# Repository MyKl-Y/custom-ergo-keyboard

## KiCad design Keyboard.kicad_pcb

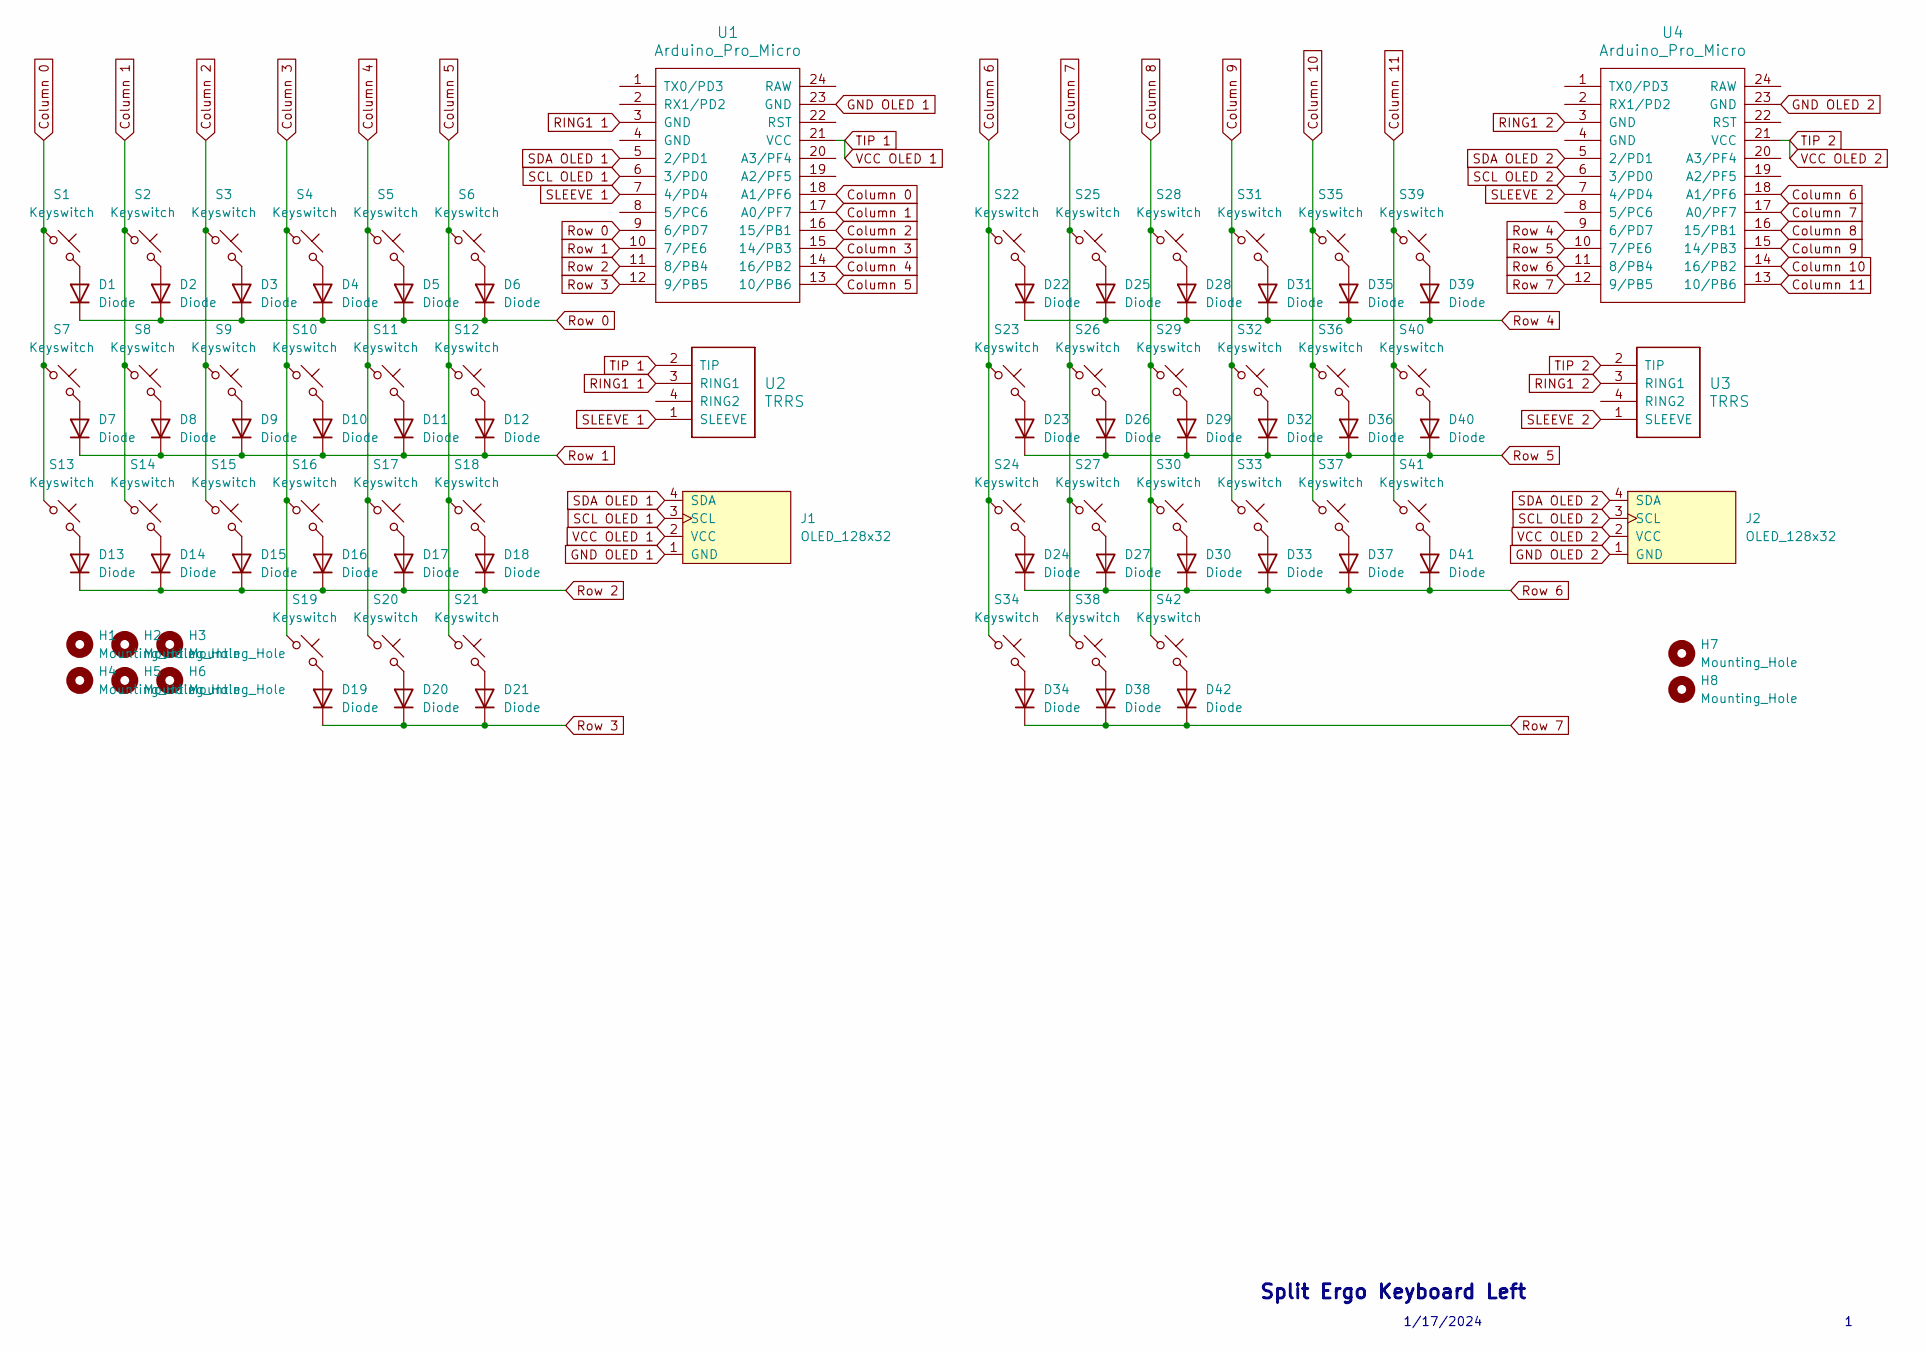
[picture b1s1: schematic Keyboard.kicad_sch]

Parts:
D1, D2, D3, D4, D5, D6, D7, D8, D9, D10, D11, D12, D13, D14, D15, D16, D17, D18, D19, D20, D21, D22, D23, D24, D25, D26, D27, D28, D29, D30, D31, D32, D33, D34, D35, D36, D37, D38, D39, D40, D41, D42: Diode; Diode_DO-35
H1, H2, H3, H4, H5, H6, H7, H8: Mounting_Hole; MountingHole_2mm
J1, J2: OLED_128x32
S1, S2, S3, S4, S5, S6, S7, S8, S9, S10, S11, S12, S13, S14, S15, S16, S17, S18, S19, S20, S22, S23, S24, S25, S26, S27, S28, S29, S30, S31, S32, S33, S35, S36, S37, S38, S39, S40, S41, S42: Keyswitch; Choc_Mini_1.00u
S21, S34: Keyswitch; Choc_Mini_1.25u
U1, U4: Arduino_Pro_Micro
U2, U3: TRRS; TRRS_PJ-320A

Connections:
Column 0: S1.1, S7.1, S13.1, U1.18 (A1/PF6)
Column 1: S2.1, S8.1, S14.1, U1.17 (A0/PF7)
Column 2: S3.1, S9.1, S15.1, U1.16 (15/PB1)
Column 3: S4.1, S10.1, S16.1, S19.1, U1.15 (14/PB3)
Column 4: S5.1, S11.1, S17.1, S20.1, U1.14 (16/PB2)
Column 5: S6.1, S12.1, S18.1, S21.1, U1.13 (10/PB6)
Column 6: S22.1, S23.1, S24.1, S34.1, U4.18 (A1/PF6)
Column 7: S25.1, S26.1, S27.1, S38.1, U4.17 (A0/PF7)
Column 8: S28.1, S29.1, S30.1, S42.1, U4.16 (15/PB1)
Column 9: S31.1, S32.1, S33.1, U4.15 (14/PB3)
Column 10: S35.1, S36.1, S37.1, U4.14 (16/PB2)
Column 11: S39.1, S40.1, S41.1, U4.13 (10/PB6)
GND OLED 1: J1.1 (GND), U1.23 (GND)
GND OLED 2: J2.1 (GND), U4.23 (GND)
unnamed: D1.2 (A), S1.2
unnamed: D2.2 (A), S2.2
unnamed: D3.2 (A), S3.2
unnamed: D4.2 (A), S4.2
unnamed: D5.2 (A), S5.2
unnamed: D6.2 (A), S6.2
unnamed: D7.2 (A), S7.2
unnamed: D8.2 (A), S8.2
unnamed: D9.2 (A), S9.2
unnamed: D10.2 (A), S10.2
unnamed: D11.2 (A), S11.2
unnamed: D12.2 (A), S12.2
unnamed: D13.2 (A), S13.2
unnamed: D14.2 (A), S14.2
unnamed: D15.2 (A), S15.2
unnamed: D16.2 (A), S16.2
unnamed: D17.2 (A), S17.2
unnamed: D18.2 (A), S18.2
unnamed: D19.2 (A), S19.2
unnamed: D20.2 (A), S20.2
unnamed: D21.2 (A), S21.2
unnamed: D22.2 (A), S22.2
unnamed: D23.2 (A), S23.2
unnamed: D24.2 (A), S24.2
unnamed: D25.2 (A), S25.2
unnamed: D26.2 (A), S26.2
unnamed: D27.2 (A), S27.2
unnamed: D28.2 (A), S28.2
unnamed: D29.2 (A), S29.2
unnamed: D30.2 (A), S30.2
unnamed: D31.2 (A), S31.2
unnamed: D32.2 (A), S32.2
unnamed: D33.2 (A), S33.2
unnamed: D34.2 (A), S34.2
unnamed: D35.2 (A), S35.2
unnamed: D36.2 (A), S36.2
unnamed: D37.2 (A), S37.2
unnamed: D38.2 (A), S38.2
unnamed: D39.2 (A), S39.2
unnamed: D40.2 (A), S40.2
unnamed: D41.2 (A), S41.2
unnamed: D42.2 (A), S42.2
RING1 1: U1.3 (GND), U2.3 (RING1)
RING1 2: U3.3 (RING1), U4.3 (GND)
Row 0: D1.1 (K), D2.1 (K), D3.1 (K), D4.1 (K), D5.1 (K), D6.1 (K), U1.9 (6/PD7)
Row 1: D7.1 (K), D8.1 (K), D9.1 (K), D10.1 (K), D11.1 (K), D12.1 (K), U1.10 (7/PE6)
Row 2: D13.1 (K), D14.1 (K), D15.1 (K), D16.1 (K), D17.1 (K), D18.1 (K), U1.11 (8/PB4)
Row 3: D19.1 (K), D20.1 (K), D21.1 (K), U1.12 (9/PB5)
Row 4: D22.1 (K), D25.1 (K), D28.1 (K), D31.1 (K), D35.1 (K), D39.1 (K), U4.9 (6/PD7)
Row 5: D23.1 (K), D26.1 (K), D29.1 (K), D32.1 (K), D36.1 (K), D40.1 (K), U4.10 (7/PE6)
Row 6: D24.1 (K), D27.1 (K), D30.1 (K), D33.1 (K), D37.1 (K), D41.1 (K), U4.11 (8/PB4)
Row 7: D34.1 (K), D38.1 (K), D42.1 (K), U4.12 (9/PB5)
SCL OLED 1: J1.3 (SCL), U1.6 (3/PD0)
SCL OLED 2: J2.3 (SCL), U4.6 (3/PD0)
SDA OLED 1: J1.4 (SDA), U1.5 (2/PD1)
SDA OLED 2: J2.4 (SDA), U4.5 (2/PD1)
SLEEVE 1: U1.7 (4/PD4), U2.1 (SLEEVE)
SLEEVE 2: U3.1 (SLEEVE), U4.7 (4/PD4)
TIP 1: J1.2 (VCC), U1.21 (VCC), U2.2 (TIP)
TIP 2: J2.2 (VCC), U3.2 (TIP), U4.21 (VCC)

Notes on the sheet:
1/17/2024
Split Ergo Keyboard Left

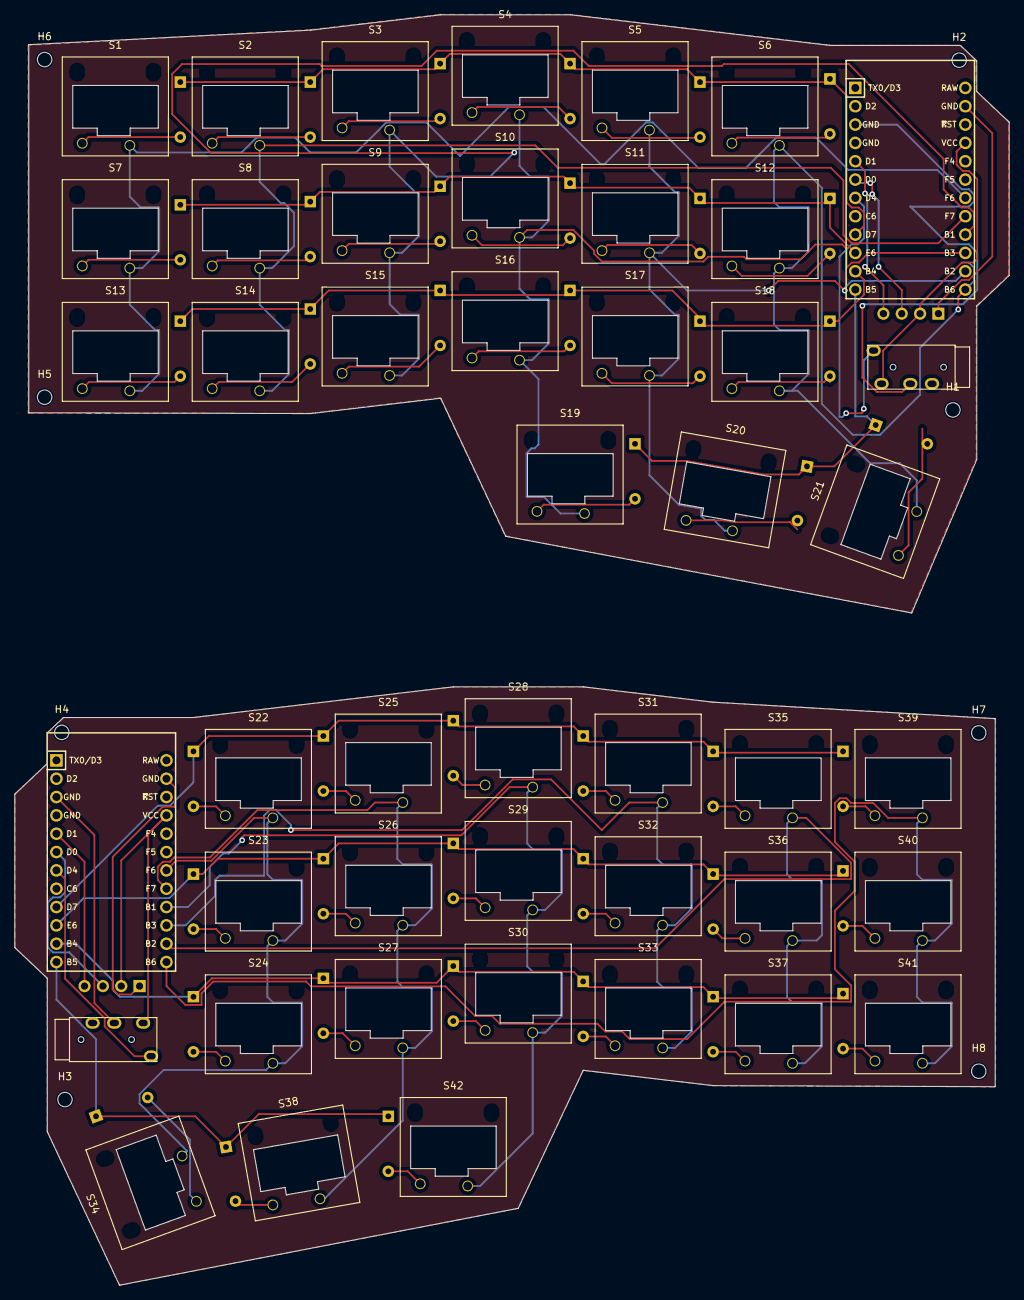
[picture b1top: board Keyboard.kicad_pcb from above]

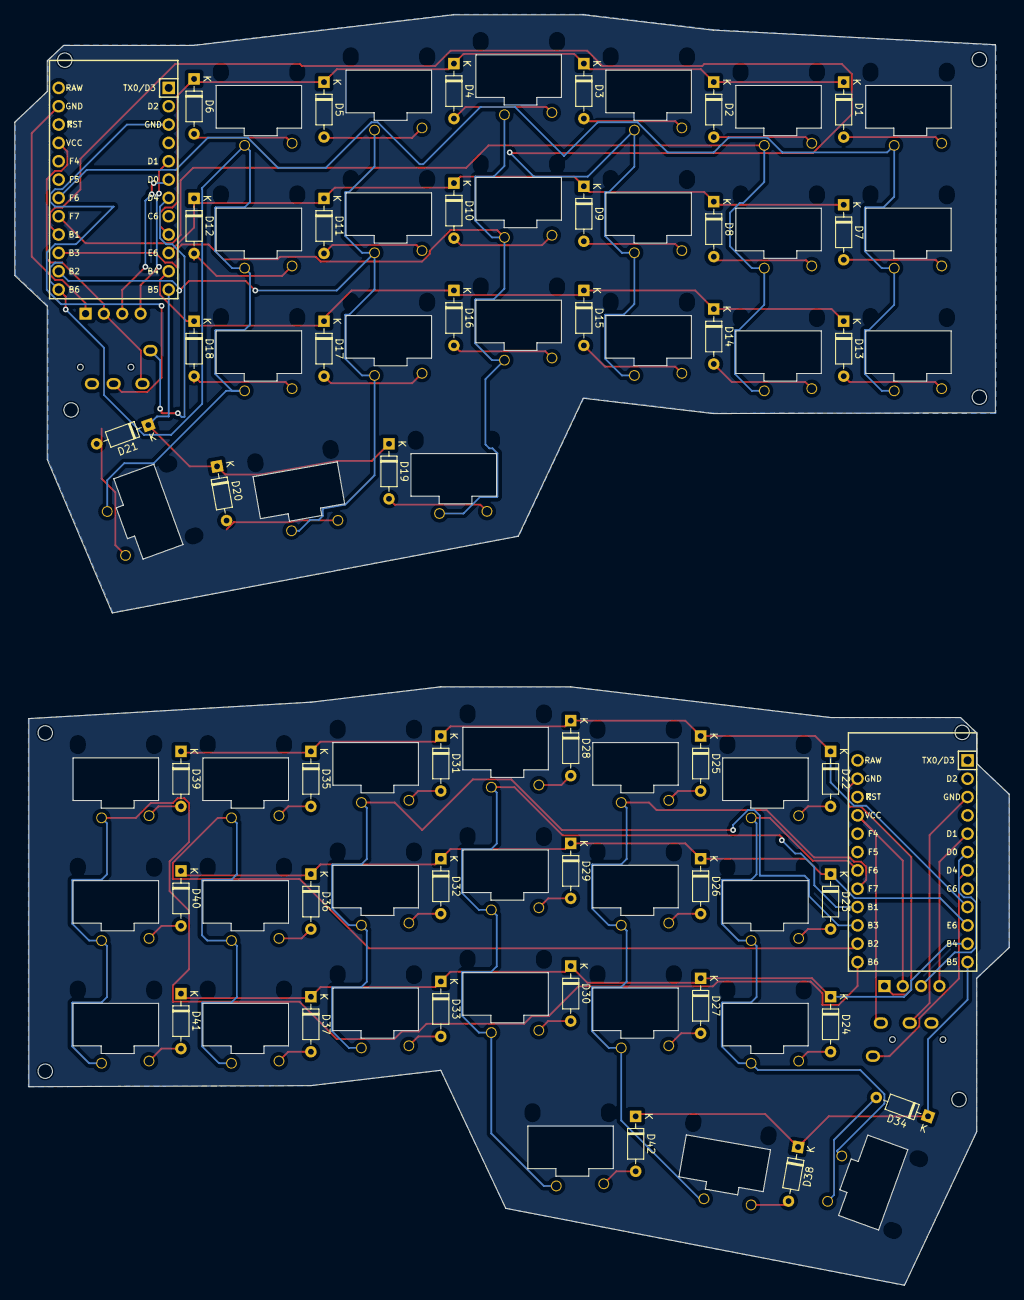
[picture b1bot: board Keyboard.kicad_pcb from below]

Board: 2 copper layers, 137.8 x 176.0 mm, 98 parts (42 on the bottom side), 74 nets.
